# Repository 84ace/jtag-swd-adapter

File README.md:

<div id="top"></div>
<!--
*** Thanks for checking out the Best-README-Template. If you have a suggestion
*** that would make this better, please fork the repo and create a pull request
*** or simply open an issue with the tag "enhancement".
*** Don't forget to give the project a star!
*** Thanks again! Now go create something AMAZING! :D
-->

<!-- PROJECT SHIELDS -->
<!--
*** I'm using markdown "reference style" links for readability.
*** Reference links are enclosed in brackets [ ] instead of parentheses ( ).
*** See the bottom of this document for the declaration of the reference variables
*** for contributors-url, forks-url, etc. This is an optional, concise syntax you may use.
*** https://www.markdownguide.org/basic-syntax/#reference-style-links
-->
[![Contributors][contributors-shield]][contributors-url]
[![Forks][forks-shield]][forks-url]
[![Stargazers][stars-shield]][stars-url]
[![Issues][issues-shield]][issues-url]
[![MIT License][license-shield]][license-url]

<!-- PROJECT LOGO -->
<br />
<div align="center">

  <h3 align="center">JTAG SWD Adapter | 1.27mm and 2.54mm cable connectors</h3>

  <p align="center">
    With selectable 1.8V, 3.3V or passthrough VTref
    <br />
    <a href="https://github.com/84ace/jtag-swd-adapter/issues">Report Bug</a>
    ·
    <a href="https://github.com/84ace/jtag-swd-adapter/issues">Request Feature</a>
  </p>
</div>

<!-- TABLE OF CONTENTS -->
<details>
  <summary>Table of Contents</summary>
  <ol>
    <li>
      <a href="#about-the-project">About The Project</a>
      <ul>
        <li><a href="#built-with">Built With</a></li>
      </ul>
    </li>
    <li>
      <a href="#getting-started">Getting Started</a>
      <ul>
        <li><a href="#prerequisites">Prerequisites</a></li>
        <li><a href="#installation">Installation</a></li>
      </ul>
    </li>
    <li><a href="#usage">Usage</a></li>
    <li><a href="#roadmap">Roadmap</a></li>
    <li><a href="#contributing">Contributing</a></li>
    <li><a href="#license">License</a></li>
    <li><a href="#contact">Contact</a></li>
    <li><a href="#acknowledgments">Acknowledgments</a></li>
  </ol>
</details>

<!-- ABOUT THE PROJECT -->
## About The Project

[![JTAG SWD Apadter][product-screenshot]](images/adapter_iso.webp)

This is a simple adapter board that allows you to interconnect various different SWD cables to your 20 pin Jlink or 10 pin Jlink EDU Mini. It also has the ability to set a VTref voltage, should you wind up in a situation where you've accidently wiped certain registers.

Here's why this adapter board exists:
* It's hard to find anything off the shelf that does what this does, and is available to buy
* It's a handy tool to have while doing embedded development

If it's lacking any features please create a ticket.

<p align="right">(<a href="#top">back to top</a>)</p>

### How to buy

Head over to the store

* [Ace's Electronics](https://aceselectronics.store)

<p align="right">(<a href="#top">back to top</a>)</p>

### Built With

You'll need the following to make modifications to the projecy

* [KiCAD](https://www.kicad.org/download/)

<p align="right">(<a href="#top">back to top</a>)</p>

<!-- GETTING STARTED -->
## Getting Started

This is an example of how you may give instructions on setting up your project locally.
To get a local copy up and running follow these simple example steps.

<!-- ROADMAP -->
## Roadmap

- [x] Add support for 20 pin Jlink
- [x] Add support for 10 pin Jlink
- [x] Add configurable VTref

See the [open issues](https://github.com/84ace/jtag-swd-adapter/issues) for a full list of proposed features (and known issues).

<p align="right">(<a href="#top">back to top</a>)</p>

<!-- CONTRIBUTING -->
## Contributing

Contributions are what make the open source community such an amazing place to learn, inspire, and create. Any contributions you make are **greatly appreciated**.

If you have a suggestion that would make this better, please fork the repo and create a pull request. You can also simply open an issue with the tag "enhancement".
Don't forget to give the project a star! Thanks again!

1. Fork the Project
2. Create your Feature Branch (`git checkout -b feature/AmazingFeature`)
3. Commit your Changes (`git commit -m 'Add some AmazingFeature'`)
4. Push to the Branch (`git push origin feature/AmazingFeature`)
5. Open a Pull Request

<p align="right">(<a href="#top">back to top</a>)</p>

<!-- LICENSE -->
## License

Distributed under the MIT License. See `LICENSE.txt` for more information.

<p align="right">(<a href="#top">back to top</a>)</p>

<!-- CONTACT -->
## Contact

Ace's Electronics - [Store](aceselectronics.store)

Acea Quigg - [@aceaquigg](https://twitter.com/aceaquigg)

Project Link: [https://github.com/84ace/jtag-swd-adapter](https://github.com/84ace/jtag-swd-adapter)

<p align="right">(<a href="#top">back to top</a>)</p>

<!-- MARKDOWN LINKS & IMAGES -->
<!-- https://www.markdownguide.org/basic-syntax/#reference-style-links -->
[contributors-shield]: https://img.shields.io/github/contributors/84ace/jtag-swd-adapter.svg?style=for-the-badge
[contributors-url]: https://github.com/84ace/jtag-swd-adapter/graphs/contributors
[forks-shield]: https://img.shields.io/github/forks/84ace/jtag-swd-adapter.svg?style=for-the-badge
[forks-url]: https://github.com/84ace/jtag-swd-adapter/network/members
[stars-shield]: https://img.shields.io/github/stars/84ace/jtag-swd-adapter.svg?style=for-the-badge
[stars-url]: https://github.com/84ace/jtag-swd-adapter/stargazers
[issues-shield]: https://img.shields.io/github/issues/84ace/jtag-swd-adapter.svg?style=for-the-badge
[issues-url]: https://github.com/84ace/jtag-swd-adapter/issues
[license-shield]: https://img.shields.io/github/license/othneildrew/Best-README-Template.svg?style=for-the-badge
[license-url]: https://github.com/84ace/jtag-swd-adapter/blob/master/LICENSE.txt
[product-screenshot]: images/adapter_iso.webp

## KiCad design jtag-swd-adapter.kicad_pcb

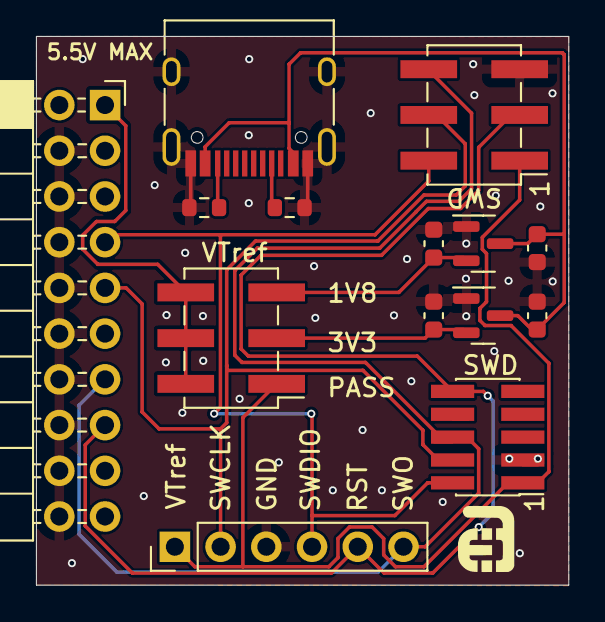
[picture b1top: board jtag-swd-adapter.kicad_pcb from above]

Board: 2 copper layers, 29.6 x 30.5 mm, 14 parts (0 on the bottom side), 12 nets.

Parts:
C1, C2, C3, C4: 1u; C_0603_1608Metric
J1: Conn_02x05_Odd_Even; PinHeader_2x05_P1.27mm_Vertical_SMD
J2, J5: Conn_02x03_Odd_Even; PinHeader_2x03_P2.54mm_Vertical_SMD
J3: Conn_01x06; PinHeader_1x06_P2.54mm_Vertical
J4: Conn_02x10_Odd_Even; PinSocket_2x10_P2.54mm_Horizontal
J6: USB_C_Receptacle_USB2.0; USB_C_Receptacle_HRO_TYPE-C-31-M-12
R1, R2: 5.1k; R_0603_1608Metric
U1: 1.8V LDO; SOT-23
U2: 3.3V LDO; SOT-23

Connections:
+1V8: C2.1, J2.5, U1.2 (VO)
+3V3: C4.1, J2.3, U2.2 (VO)
+5V: C1.1, C3.1, J6.A4 (VBUS), J6.A9 (VBUS), J6.B4 (VBUS), J6.B9 (VBUS), U1.3 (VI), U2.3 (VI)
/RESET: J1.10, J3.5, J4.15, J5.3
/SWDCLK\TCK: J1.4, J3.2, J4.9, J5.4
/SWDIO\TMS: J1.2, J3.4, J4.7, J5.2
/SWO\TDO: J1.6, J3.6, J4.13, J5.6
/VTref: J2.2, J2.4, J2.6, J4.1
/VTrefJ: J1.1, J2.1, J3.1, J5.1
GND: C1.2, C2.2, C3.2, C4.2, J1.3, J3.3, J4.4, J4.6, J4.8, J4.10, J4.12, J4.14, J4.16, J4.18, J4.20, J5.5, J6.A1 (GND), J6.A12 (GND), J6.B1 (GND), J6.B12 (GND), J6.S1 (SHIELD), R1.1, R2.1, U1.1 (GND), U2.1 (GND)
unnamed: J6.A5 (CC1), R1.2
unnamed: J6.B5 (CC2), R2.2

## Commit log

2022-06-22 first push
2022-06-22 updated all links
